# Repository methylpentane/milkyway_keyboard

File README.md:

# milkyway 65% keyboard pcb & plate
This repository contains kicad file (PCB/schematic), no firmware here.

This repository based on [GL516 Design Template](https://github.com/Salicylic-acid3/GL516_Template) by Salicylic-acid3.

# feature
- 65% keyboard that neatly looks like Tsangan-layout.
- Several layout options on center area(milkyway-area).
    - macro
    - rotary encoders
    - numpad (with sacrificing symbol keys on righthand)
- Also there will be some layout options on R5.
    - split spacebars
    - one more rotary encoder
    - 8u & 10u spacebar 🤔

# supported layout

- about keys that have "ENC" written, you can choose whether to implement keyswitch or encoder.
    - For ENC1a and ENC1b, only one of the encoders can be implemented. and the same for ENC5a and ENC5b.
- some layouts force northfacing switch (switch with "N")

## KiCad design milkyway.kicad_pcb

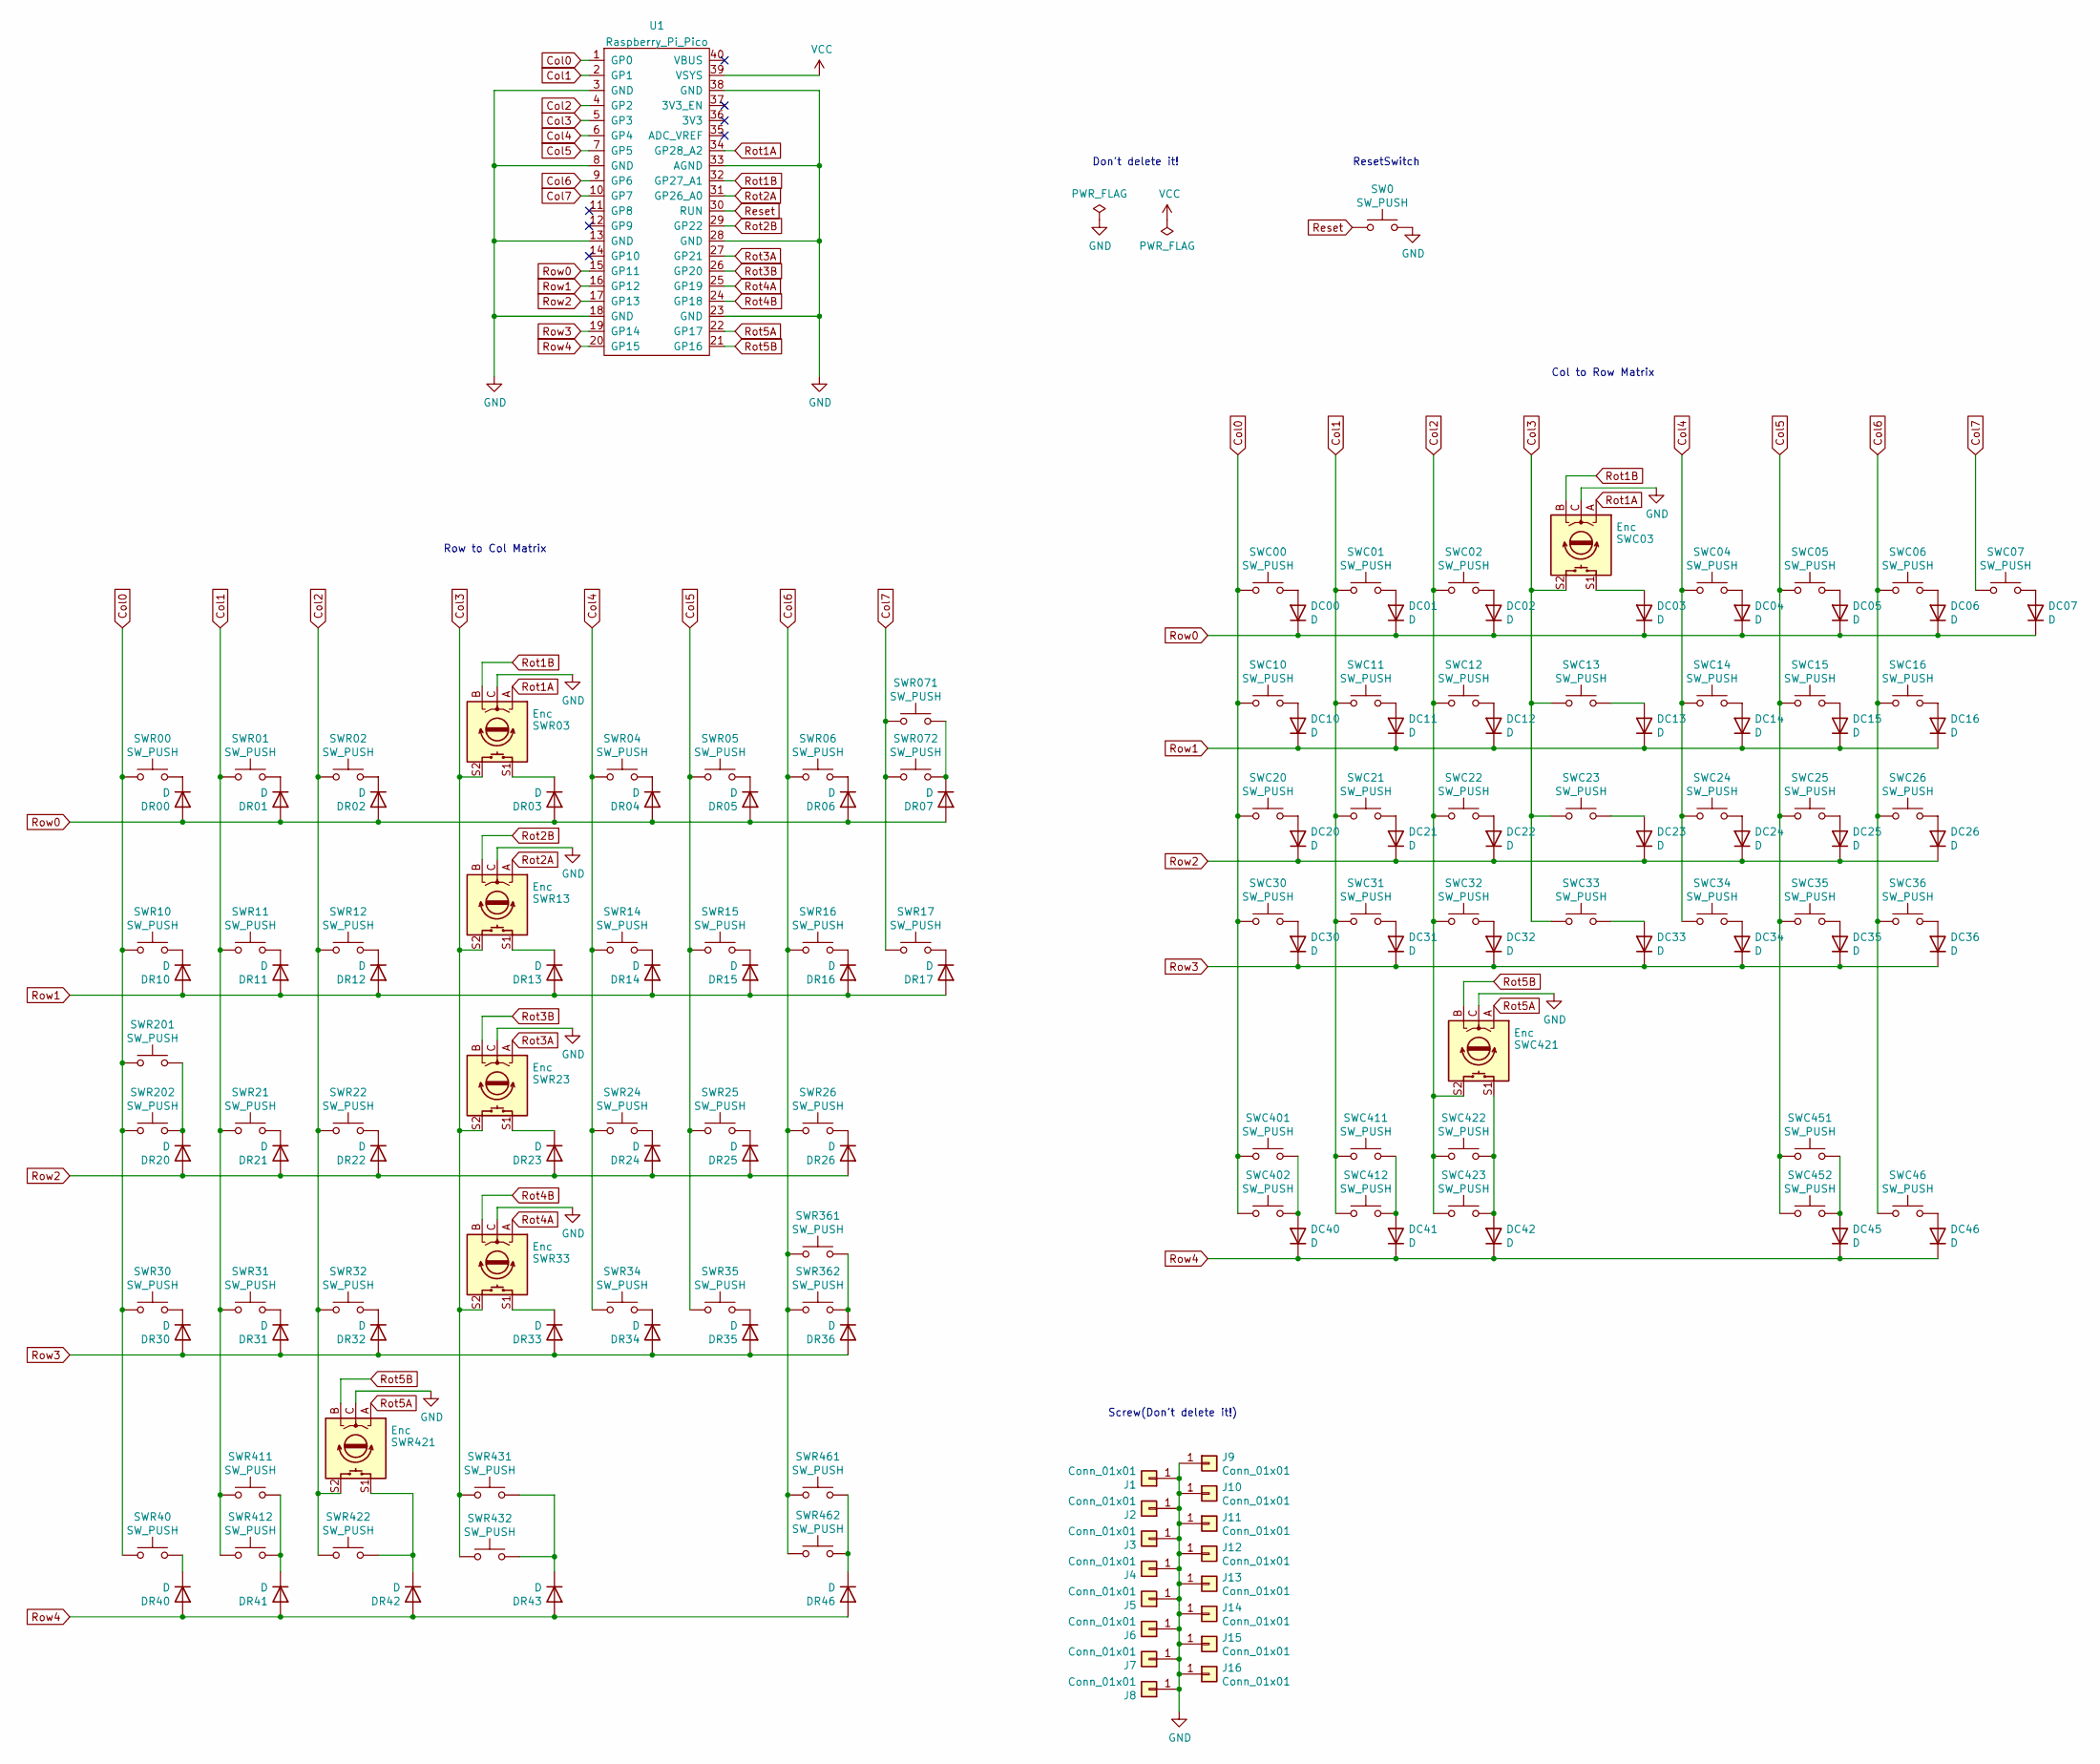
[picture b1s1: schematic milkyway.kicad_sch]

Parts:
DC00, DC01, DC02, DC03, DC04, DC05, DC06, DC07, DC10, DC11, DC12, DC13, DC14, DC15, DC16, DC20, DC21, DC22, DC23, DC24, DC25, DC26, DC30, DC31, DC32, DC33, DC34, DC35, DC36, DC40, DC41, DC42, DC45, DC46: D; Diode_TH_SMD
DR00, DR01, DR02, DR03, DR04, DR05, DR06, DR07, DR10, DR11, DR12, DR13, DR14, DR15, DR16, DR17, DR20, DR21, DR22, DR23, DR24, DR25, DR26, DR30, DR31, DR32, DR33, DR34, DR35, DR36, DR40, DR41, DR42, DR43, DR46: D; Diode_TH_SMD
J1, J2, J3, J4, J5, J6: Conn_01x01; m2_Screw_Hole_EdgeCuts
J7, J8, J9, J10, J11, J12, J13, J14, J15, J16: Conn_01x01; m2_Screw_Hole_Fab
SW0: SW_PUSH; ResetSW
SWC00, SWC01, SWC02, SWC04, SWC05, SWC06, SWC07, SWC10, SWC11, SWC12, SWC13, SWC14, SWC15, SWC16, SWC20, SWC21, SWC22, SWC23, SWC24, SWC25, SWC30, SWC31, SWC32, SWC33, SWC34, SWC35, SWC36, SWC401: SW_PUSH; CherryMX_Hotswap_1u
SWC03: Enc; CherryMX_Hotswap_1u_EC12
SWC26: SW_PUSH; CherryMX_Hotswap_2.25u
SWC46, SWC402, SWC451, SWC452: SW_PUSH; CherryMX_Hotswap_1.5u
SWC411: SW_PUSH; CherryMX_Solder_3u_Rev
SWC412: SW_PUSH; CherryMX_1u_solder
SWC421: Enc; CherryMX_Solder_1u_EC12
SWC422: SW_PUSH; CherryMX_Solder_8u7u_Rev
SWC423: SW_PUSH; CherryMX_Solder_2.75u_Rev
SWR00, SWR01, SWR02, SWR04, SWR05, SWR06, SWR11, SWR12, SWR14, SWR15, SWR16, SWR21, SWR22, SWR24, SWR25, SWR26, SWR31, SWR32, SWR34, SWR35, SWR072, SWR202, SWR461: SW_PUSH; CherryMX_Hotswap_1u
SWR03, SWR13, SWR23, SWR33: Enc; CherryMX_Hotswap_1u_EC12
SWR10, SWR17, SWR40, SWR411, SWR412, SWR462: SW_PUSH; CherryMX_Hotswap_1.5u
SWR30, SWR361: SW_PUSH; CherryMX_Hotswap_2.75u
SWR071: SW_PUSH; CherryMX_Hotswap_2u
SWR201, SWR362: SW_PUSH; CherryMX_Hotswap_1.75u
SWR421: Enc; CherryMX_Solder_1u_EC12
SWR422: SW_PUSH; CherryMX_Solder_2u_Rev
SWR431: SW_PUSH; CherryMX_Solder_3u_Rev
SWR432: SW_PUSH; CherryMX_Solder_2.25u_Rev
U1: Raspberry_Pi_Pico

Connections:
Col0: SWC00.1, SWC10.1, SWC20.1, SWC30.1, SWC401.1, SWC402.1, SWR00.1, SWR10.1, SWR30.1, SWR40.1, SWR201.1, SWR202.1, U1.1 (GP0)
Col1: SWC01.1, SWC11.1, SWC21.1, SWC31.1, SWC411.1, SWC412.1, SWR01.1, SWR11.1, SWR21.1, SWR31.1, SWR411.1, SWR412.1, U1.2 (GP1)
Col2: SWC02.1, SWC12.1, SWC22.1, SWC32.1, SWC421.S2, SWC422.1, SWC423.1, SWR02.1, SWR12.1, SWR22.1, SWR32.1, SWR421.S2, SWR422.1, U1.4 (GP2)
Col3: SWC03.S2, SWC13.1, SWC23.1, SWC33.1, SWR03.S2, SWR13.S2, SWR23.S2, SWR33.S2, SWR431.1, SWR432.1, U1.5 (GP3)
Col4: SWC04.1, SWC14.1, SWC24.1, SWC34.1, SWR04.1, SWR14.1, SWR24.1, SWR34.1, U1.6 (GP4)
Col5: SWC05.1, SWC15.1, SWC25.1, SWC35.1, SWC451.1, SWC452.1, SWR05.1, SWR15.1, SWR25.1, SWR35.1, U1.7 (GP5)
Col6: SWC06.1, SWC16.1, SWC26.1, SWC36.1, SWC46.1, SWR06.1, SWR16.1, SWR26.1, SWR361.1, SWR362.1, SWR461.1, SWR462.1, U1.9 (GP6)
Col7: SWC07.1, SWR17.1, SWR071.1, SWR072.1, U1.10 (GP7)
GND: J1.1, J2.1, J3.1, J4.1, J5.1, J6.1, J7.1, J8.1, J9.1, J10.1, J11.1, J12.1, J13.1, J14.1, J15.1, J16.1, SW0.2, SWC03.C, SWC421.C, SWR03.C, SWR13.C, SWR23.C, SWR33.C, SWR421.C, U1.3 (GND), U1.8 (GND), U1.13 (GND), U1.18 (GND), U1.23 (GND), U1.28 (GND), U1.33 (AGND), U1.38 (GND)
unnamed: DC00.2 (A), SWC00.2
unnamed: DC01.2 (A), SWC01.2
unnamed: DC02.2 (A), SWC02.2
unnamed: DC03.2 (A), SWC03.S1
unnamed: DC04.2 (A), SWC04.2
unnamed: DC05.2 (A), SWC05.2
unnamed: DC06.2 (A), SWC06.2
unnamed: DC07.2 (A), SWC07.2
unnamed: DC10.2 (A), SWC10.2
unnamed: DC11.2 (A), SWC11.2
unnamed: DC12.2 (A), SWC12.2
unnamed: DC13.2 (A), SWC13.2
unnamed: DC14.2 (A), SWC14.2
unnamed: DC15.2 (A), SWC15.2
unnamed: DC16.2 (A), SWC16.2
unnamed: DC20.2 (A), SWC20.2
unnamed: DC21.2 (A), SWC21.2
unnamed: DC22.2 (A), SWC22.2
unnamed: DC23.2 (A), SWC23.2
unnamed: DC24.2 (A), SWC24.2
unnamed: DC25.2 (A), SWC25.2
unnamed: DC26.2 (A), SWC26.2
unnamed: DC30.2 (A), SWC30.2
unnamed: DC31.2 (A), SWC31.2
unnamed: DC32.2 (A), SWC32.2
unnamed: DC33.2 (A), SWC33.2
unnamed: DC34.2 (A), SWC34.2
unnamed: DC35.2 (A), SWC35.2
unnamed: DC36.2 (A), SWC36.2
unnamed: DC40.2 (A), SWC401.2, SWC402.2
unnamed: DC41.2 (A), SWC411.2, SWC412.2
unnamed: DC42.2 (A), SWC421.S1, SWC422.2, SWC423.2
unnamed: DC45.2 (A), SWC451.2, SWC452.2
unnamed: DC46.2 (A), SWC46.2
unnamed: DR00.1 (K), SWR00.2
unnamed: DR01.1 (K), SWR01.2
unnamed: DR02.1 (K), SWR02.2
unnamed: DR03.1 (K), SWR03.S1
unnamed: DR04.1 (K), SWR04.2
unnamed: DR05.1 (K), SWR05.2
unnamed: DR06.1 (K), SWR06.2
unnamed: DR07.1 (K), SWR071.2, SWR072.2
unnamed: DR10.1 (K), SWR10.2
unnamed: DR11.1 (K), SWR11.2
unnamed: DR12.1 (K), SWR12.2
unnamed: DR13.1 (K), SWR13.S1
unnamed: DR14.1 (K), SWR14.2
unnamed: DR15.1 (K), SWR15.2
unnamed: DR16.1 (K), SWR16.2
unnamed: DR17.1 (K), SWR17.2
unnamed: DR20.1 (K), SWR201.2, SWR202.2
unnamed: DR21.1 (K), SWR21.2
unnamed: DR22.1 (K), SWR22.2
unnamed: DR23.1 (K), SWR23.S1
unnamed: DR24.1 (K), SWR24.2
unnamed: DR25.1 (K), SWR25.2
unnamed: DR26.1 (K), SWR26.2
unnamed: DR30.1 (K), SWR30.2
unnamed: DR31.1 (K), SWR31.2
unnamed: DR32.1 (K), SWR32.2
unnamed: DR33.1 (K), SWR33.S1
unnamed: DR34.1 (K), SWR34.2
unnamed: DR35.1 (K), SWR35.2
unnamed: DR36.1 (K), SWR361.2, SWR362.2
unnamed: DR40.1 (K), SWR40.2
unnamed: DR41.1 (K), SWR411.2, SWR412.2
unnamed: DR42.1 (K), SWR421.S1, SWR422.2
unnamed: DR43.1 (K), SWR431.2, SWR432.2
unnamed: DR46.1 (K), SWR461.2, SWR462.2
Reset: SW0.1, U1.30 (RUN)
Rot1A: SWC03.A, SWR03.A, U1.34 (GP28_A2)
Rot1B: SWC03.B, SWR03.B, U1.32 (GP27_A1)
Rot2A: SWR13.A, U1.31 (GP26_A0)
Rot2B: SWR13.B, U1.29 (GP22)
Rot3A: SWR23.A, U1.27 (GP21)
Rot3B: SWR23.B, U1.26 (GP20)
Rot4A: SWR33.A, U1.25 (GP19)
Rot4B: SWR33.B, U1.24 (GP18)
Rot5A: SWC421.A, SWR421.A, U1.22 (GP17)
Rot5B: SWC421.B, SWR421.B, U1.21 (GP16)
Row0: DC00.1 (K), DC01.1 (K), DC02.1 (K), DC03.1 (K), DC04.1 (K), DC05.1 (K), DC06.1 (K), DC07.1 (K), DR00.2 (A), DR01.2 (A), DR02.2 (A), DR03.2 (A), DR04.2 (A), DR05.2 (A), DR06.2 (A), DR07.2 (A), U1.15 (GP11)
Row1: DC10.1 (K), DC11.1 (K), DC12.1 (K), DC13.1 (K), DC14.1 (K), DC15.1 (K), DC16.1 (K), DR10.2 (A), DR11.2 (A), DR12.2 (A), DR13.2 (A), DR14.2 (A), DR15.2 (A), DR16.2 (A), DR17.2 (A), U1.16 (GP12)
Row2: DC20.1 (K), DC21.1 (K), DC22.1 (K), DC23.1 (K), DC24.1 (K), DC25.1 (K), DC26.1 (K), DR20.2 (A), DR21.2 (A), DR22.2 (A), DR23.2 (A), DR24.2 (A), DR25.2 (A), DR26.2 (A), U1.17 (GP13)
Row3: DC30.1 (K), DC31.1 (K), DC32.1 (K), DC33.1 (K), DC34.1 (K), DC35.1 (K), DC36.1 (K), DR30.2 (A), DR31.2 (A), DR32.2 (A), DR33.2 (A), DR34.2 (A), DR35.2 (A), DR36.2 (A), U1.19 (GP14)
Row4: DC40.1 (K), DC41.1 (K), DC42.1 (K), DC45.1 (K), DC46.1 (K), DR40.2 (A), DR41.2 (A), DR42.2 (A), DR43.2 (A), DR46.2 (A), U1.20 (GP15)
VCC: U1.39 (VSYS)

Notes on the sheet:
Screw(Don't delete it!)
Don't delete it!
ResetSwitch
Row to Col Matrix
Col to Row Matrix

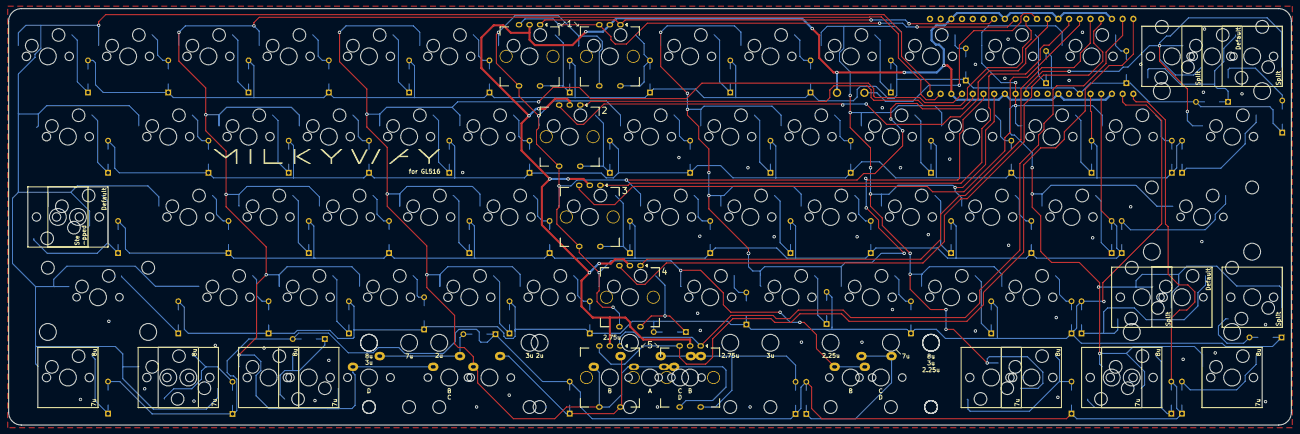
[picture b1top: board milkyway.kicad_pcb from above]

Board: 2 copper layers, 304.4 x 98.8 mm, 162 parts (0 on the bottom side), 94 nets.

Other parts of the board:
J17: Conn_01x01; m2_Screw_Hole_Fab

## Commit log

2022-02-06 first commit .
2022-02-06 first commit ..
2022-02-09 complete plate
2022-02-16 complete pcb
2022-02-16 layout image
2022-02-16 スタビバー上を通る配線を修正
2022-02-16 画像を修正
2022-02-17 プレートのkicad_proが増えた
2022-02-17 add decoration plate template
2022-02-18 footprint miss thx salicylic acid san
2022-02-18 pipicoフットプリント修正 配線かっこよく
2022-02-18 追加調整
2022-02-20 さらに追加調整
2022-02-20 さらにさらに追加調整
2022-02-21 組み立て補助のためのシルク調整
2022-02-21 image directory. design logo on back. front soon.
2022-02-21 front silk design
2022-02-22 配線クリアランス完全確保 GNDベタ Stepped CapsLock修正
2022-02-22 Stepped CapsLock修正(plate)
2022-02-23 README 更新
2022-03-02 マスクの微修正 GNDベタ 一旦削除
2022-03-02 Revert "Update README.md"
    This reverts commit f3f78b176cc35fe71f0267eae048b032c1bbfaf5.
2022-03-17 シルク完了、一旦完成。 カットデータ作成したが、現状ignore
2022-09-04 change LICENSE into CC
2022-09-04 Revert "change LICENSE into CC"
    This reverts commit 96052635ea5fd37ffb829e6136433543f28ef357.
2022-09-04 Add copyright notice for MIT. Add cc by-sa.
